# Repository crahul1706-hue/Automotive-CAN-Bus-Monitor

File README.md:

# Automotive CAN Bus Monitor and Fault Detector

An ESP32-based CAN bus monitoring and fault detection PCB designed using KiCad 10.0.

## Project Overview

This project focuses on designing a custom Printed Circuit Board (PCB) that interfaces an ESP32 DevKit V1 with a Controller Area Network (CAN) bus through an SN65HVD230 CAN transceiver.

The goal is to develop a platform for monitoring CAN communication, observing message traffic, and detecting selected communication anomalies through future firmware development.

This project demonstrates PCB schematic design, component selection, footprint assignment, PCB layout, and design-rule checking.

## Project Objectives

- Design a CAN bus interface PCB using KiCad.
- Interface an ESP32 with a CAN transceiver.
- Provide CANH, CANL, and ground connections.
- Include a selectable 120 Ω termination resistor.
- Plan firmware for CAN message monitoring and timeout detection.
- Document the design as part of an embedded systems portfolio.

## System Architecture

```text
External CAN Bus
   CANH / CANL / GND
          |
          v
 SN65HVD230 Transceiver
          |
          v
     ESP32 DevKit V1
          |
          v
     USB Serial Monitor
```

The ESP32 handles CAN protocol operations using its built-in TWAI controller, while the SN65HVD230 provides the physical interface to the CAN network.

## Hardware Components

| Component | Purpose |
|---|---|
| ESP32 DevKit V1 (38-pin) | Main controller |
| SN65HVD230 | CAN physical-layer transceiver |
| 120 Ω resistor | CAN bus termination |
| Termination jumper | Enables or disables termination |
| 10 kΩ resistor | Transceiver slope-control circuit |
| 100 nF capacitor | Supply decoupling |
| LED and series resistor | Power/status indication |
| 3-pin connector | CANH, CANL, and GND interface |

## Software and Tools

- KiCad 10.0 — schematic capture and PCB layout
- ESP32 development environment — planned firmware development
- GitHub — source files and project documentation

## PCB Design Workflow

1. Defined the circuit requirements.
2. Created the schematic in KiCad.
3. Selected components and assigned footprints.
4. Designed the PCB layout.
5. Ran Electrical Rules Checker (ERC).
6. Ran Design Rules Checker (DRC).
7. Organized the project files for documentation and version control.

## Planned Firmware Features

The following features are planned and have not yet been validated:

- Receive CAN frames.
- Display CAN identifiers and data bytes.
- Monitor message frequency.
- Detect missing periodic messages using configurable timeouts.
- Report selected communication errors.
- Log received frames through the USB serial interface.

## Repository Structure

```text
Automotive_CAN_Monitor/
├── KiCad/
│   ├── Automotive_CAN_Monitor.kicad_pro
│   ├── Automotive_CAN_Monitor.kicad_sch
│   └── Automotive_CAN_Monitor.kicad_pcb
├── Images/
│   ├── schematic.png
│   ├── pcb-layout.png
│   ├── erc-results.png
│   └── drc-results.png
├── Documentation/
│   └── component-list.md
└── README.md
```

*The filenames shown are the intended organization. Include only files and screenshots that actually exist in your repository.*

## Design Verification

The schematic and PCB were checked using KiCad ERC and DRC.

A zero-error result indicates that the reported checks passed under the configured rules. It does not guarantee correct electrical operation, successful CAN communication, or automotive-grade reliability.

The design has not been physically manufactured or tested.

## Current Project Status

 Schematic design
 Component selection
 Footprint assignment
 PCB layout
 ERC and DRC checks performed
 Final electrical and footprint review

## Future Improvements

- Develop CAN monitoring firmware.
- Test communication using a separate CAN test node.
- Add a CAN message logging utility.
- Improve documentation with verified schematics and layout images.
- Review protection circuitry and physical connector dimensions.

## Applications

- Embedded systems learning
- Automotive electronics education
- CAN communication experimentation
- PCB design and hardware development portfolio

## Disclaimer

This is an educational prototype, not an automotive-qualified diagnostic device. It has not been manufactured or validated for installation in a real vehicle. Testing should initially be performed using a controlled CAN bench setup.

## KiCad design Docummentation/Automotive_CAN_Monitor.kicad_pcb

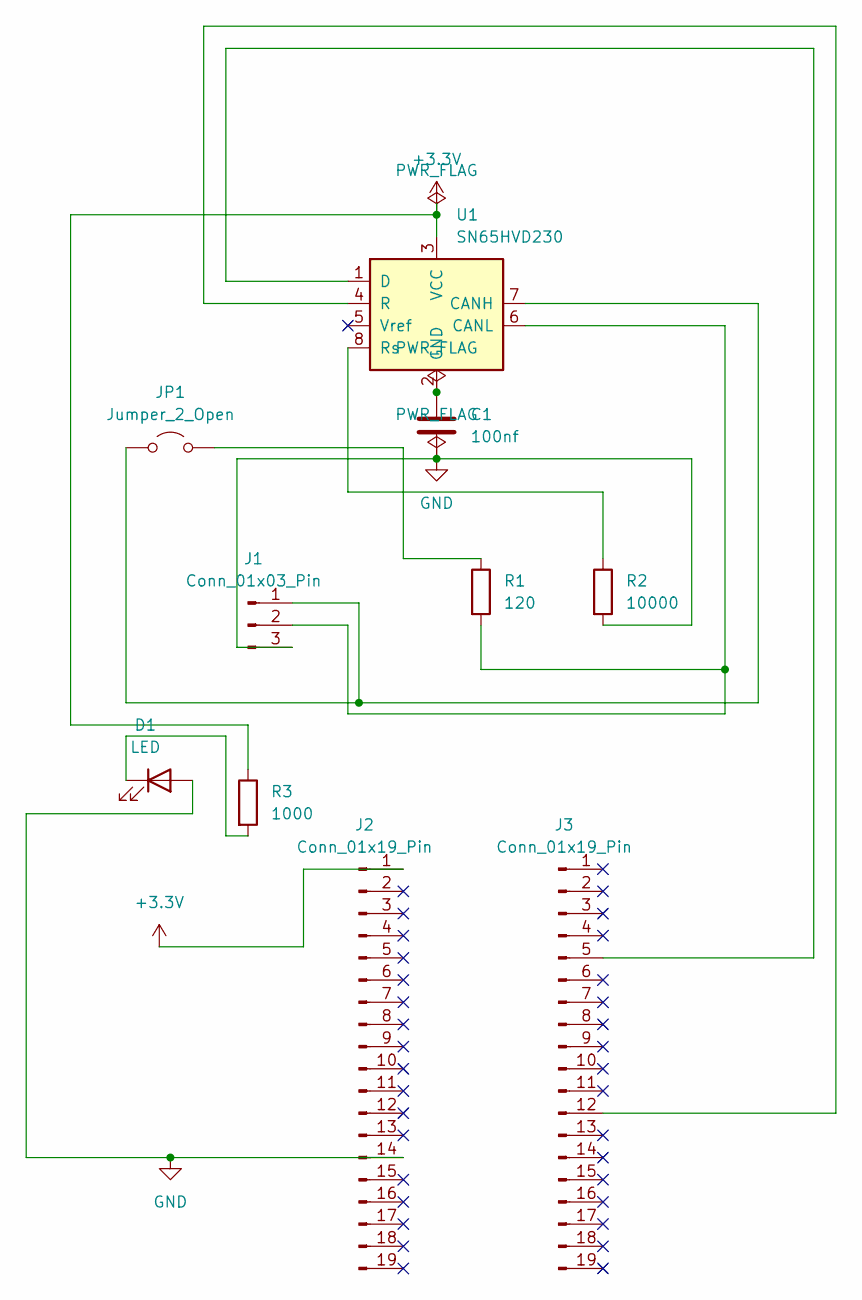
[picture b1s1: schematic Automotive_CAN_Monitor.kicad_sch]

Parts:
C1: 100nf; C_0805_2012Metric
D1: LED; LED_0805_2012Metric
J1: Conn_01x03_Pin; TerminalBlock_Phoenix_MKDS-1,5-3_1x03_P5.00mm_Horizontal
J2, J3: Conn_01x19_Pin; PinSocket_1x19_P2.54mm_Vertical
JP1: Jumper_2_Open; SolderJumper-2_P1.3mm_Open_Pad1.0x1.5mm
R1: 120; R_0805_2012Metric
R2: 10000; R_0805_2012Metric
R3: 1000; R_0805_2012Metric
U1: SN65HVD230; SOIC-8_3.9x4.9mm_P1.27mm

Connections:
+3.3V: J2.1, R3.1, U1.3 (VCC)
GND: C1.2, D1.2 (A), J1.3, J2.14, R2.2
unnamed: D1.1 (K), R3.2
unnamed: J1.1, JP1.1 (A), U1.7 (CANH)
unnamed: J1.2, R1.2, U1.6 (CANL)
unnamed: J3.5, U1.1 (D)
unnamed: J3.12, U1.4 (R)
unnamed: JP1.2 (B), R1.1
unnamed: C1.1, U1.2 (GND)
unnamed: R2.1, U1.8 (Rs)

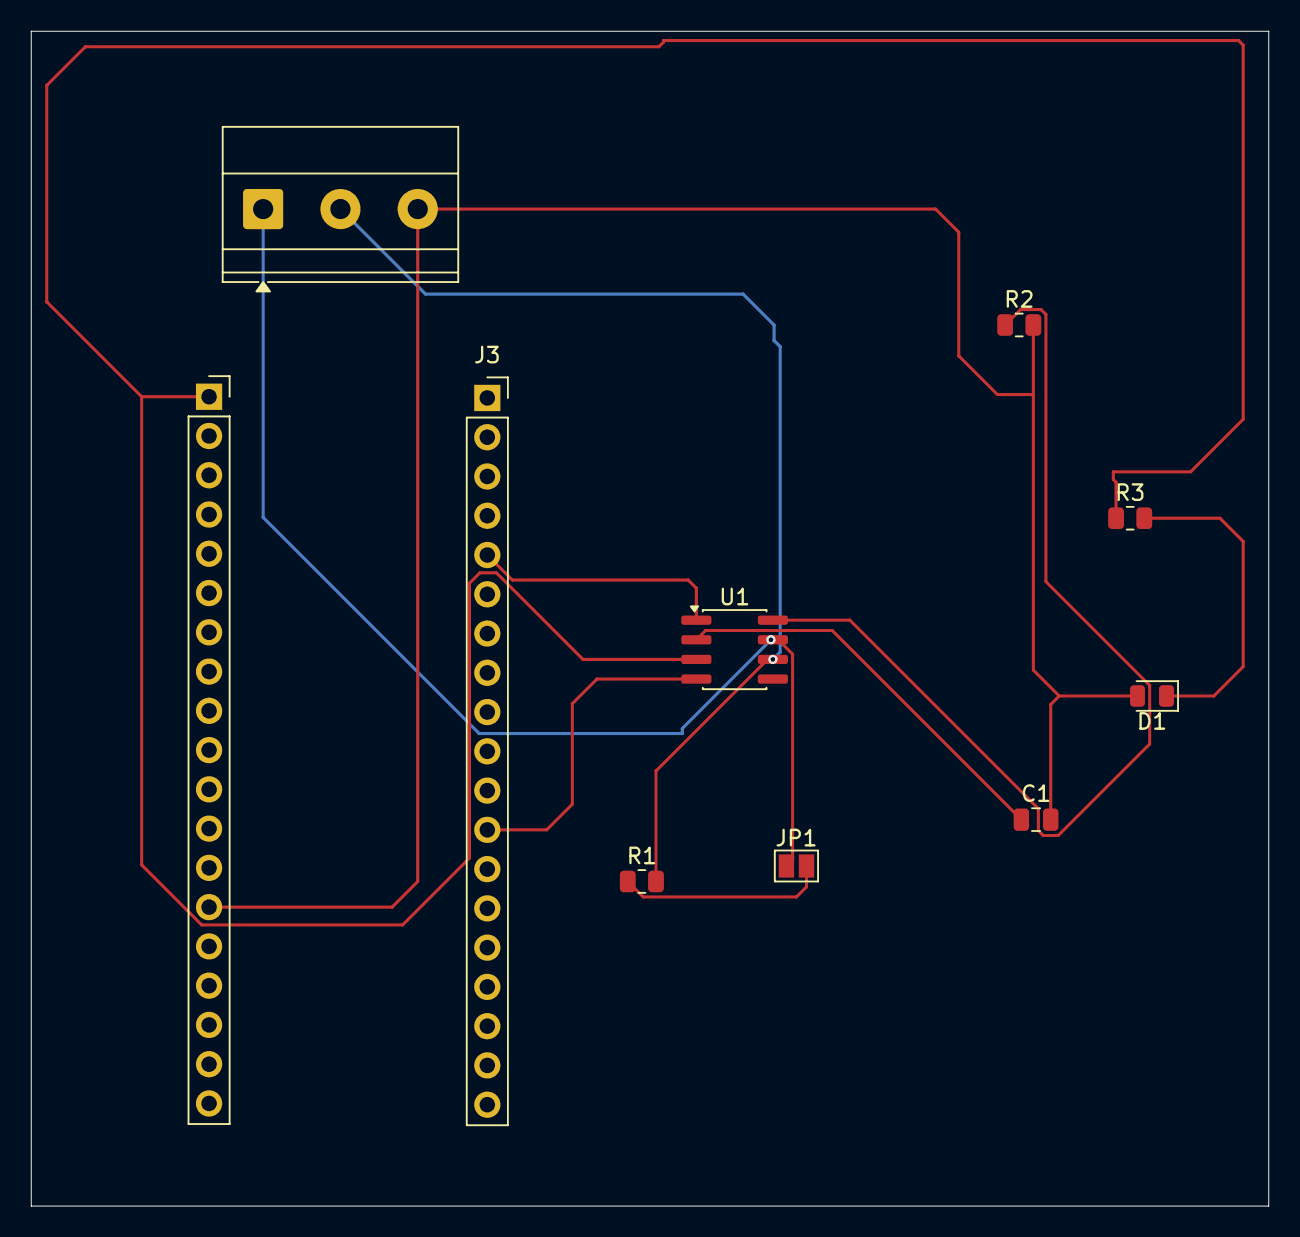
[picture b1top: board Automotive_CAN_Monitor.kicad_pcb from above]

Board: 2 copper layers, 80.0 x 76.0 mm, 10 parts (0 on the bottom side), 10 nets.
